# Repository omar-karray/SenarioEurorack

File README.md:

# SenarioEurorack

Senario Looper / MultiFX: a 24HP Eurorack module on a Daisy Seed2 DFM.

| Folder | What |
|---|---|
| [SenarioHW/](SenarioHW/README.md) | the hardware: KiCad project (schematic and primary placement), BOM, design notes |
| [SenarioOS/](SenarioOS/README.md) | the firmware (empty for now; the pin map is in `SenarioOS/docs/pinmap.md`) |
| `KicadLibs/` | git submodule: the shared KiCad libraries (private repository `omar-karray/KicadLibs`) |

## Clone

```bash
git clone --recurse-submodules https://github.com/omar-karray/SenarioEurorack.git
```

The submodule is private: you need access to `omar-karray/KicadLibs`. KiCad 10 resolves the libraries through the project's own tables (`${KIPRJMOD}/../../KicadLibs`), so no global set-up is needed for this project.

Start with [SenarioHW/docs/spec-beta.md](SenarioHW/docs/spec-beta.md) (the version-beta platform spec and how it connects to the Seed2 DFM), then [SenarioHW/docs/design-notes.md](SenarioHW/docs/design-notes.md) (first pass, still valid except where the spec replaces it).

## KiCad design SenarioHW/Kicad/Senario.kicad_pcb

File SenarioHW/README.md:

# SenarioHW

Hardware of the Senario Looper / MultiFX: a 24HP Eurorack module on a Daisy Seed2 DFM.

| Path | What |
|---|---|
| `Kicad/` | the KiCad 10 project `Senario.kicad_pro` (schematic: root + 5 sheets, PCB: primary placement, unrouted) |
| `Kicad/scripts/` | the generators; `design.py` is the design (every part, net and the floorplan) |
| `Kicad/lib/` | project symbols (`Senario.kicad_sym`, generated) |
| `docs/` | `design-notes.md` (read this first), `bom.csv`, `previews/` (schematic PDF, front and back placement, 3D renders), datasheets are in `KicadLibs/datasheets/` |

Libraries come from the `KicadLibs` submodule at the repository root (`${KIPRJMOD}/../../KicadLibs`); stock KiCad libraries for the rest.

## Generated, not drawn

The schematic and the PCB are written by scripts from `Kicad/scripts/design.py`, the same way the Tanghim boards are:

```
cd SenarioHW/Kicad
FORCE=1 scripts/build.sh      # project files, schematic sheets, PCB placement (needs KiCad 10)
scripts/previews.sh           # schematic PDF, front / back PNG, bom.csv
```

`build.sh` refuses to run when `Senario.kicad_pcb` exists, because it **overwrites the schematic and any placement you did by hand**. Use it until you start moving parts in KiCad; from then on edit in KiCad (or export your placement before rebuilding).

Checks that pass on this version: ERC 0 violations; the schematic's netlist and the PCB pad nets are identical (`scripts/check_netlist.py`, 841 pads); DRC shows no placement errors, only the unrouted connections (499) and silkscreen warnings.

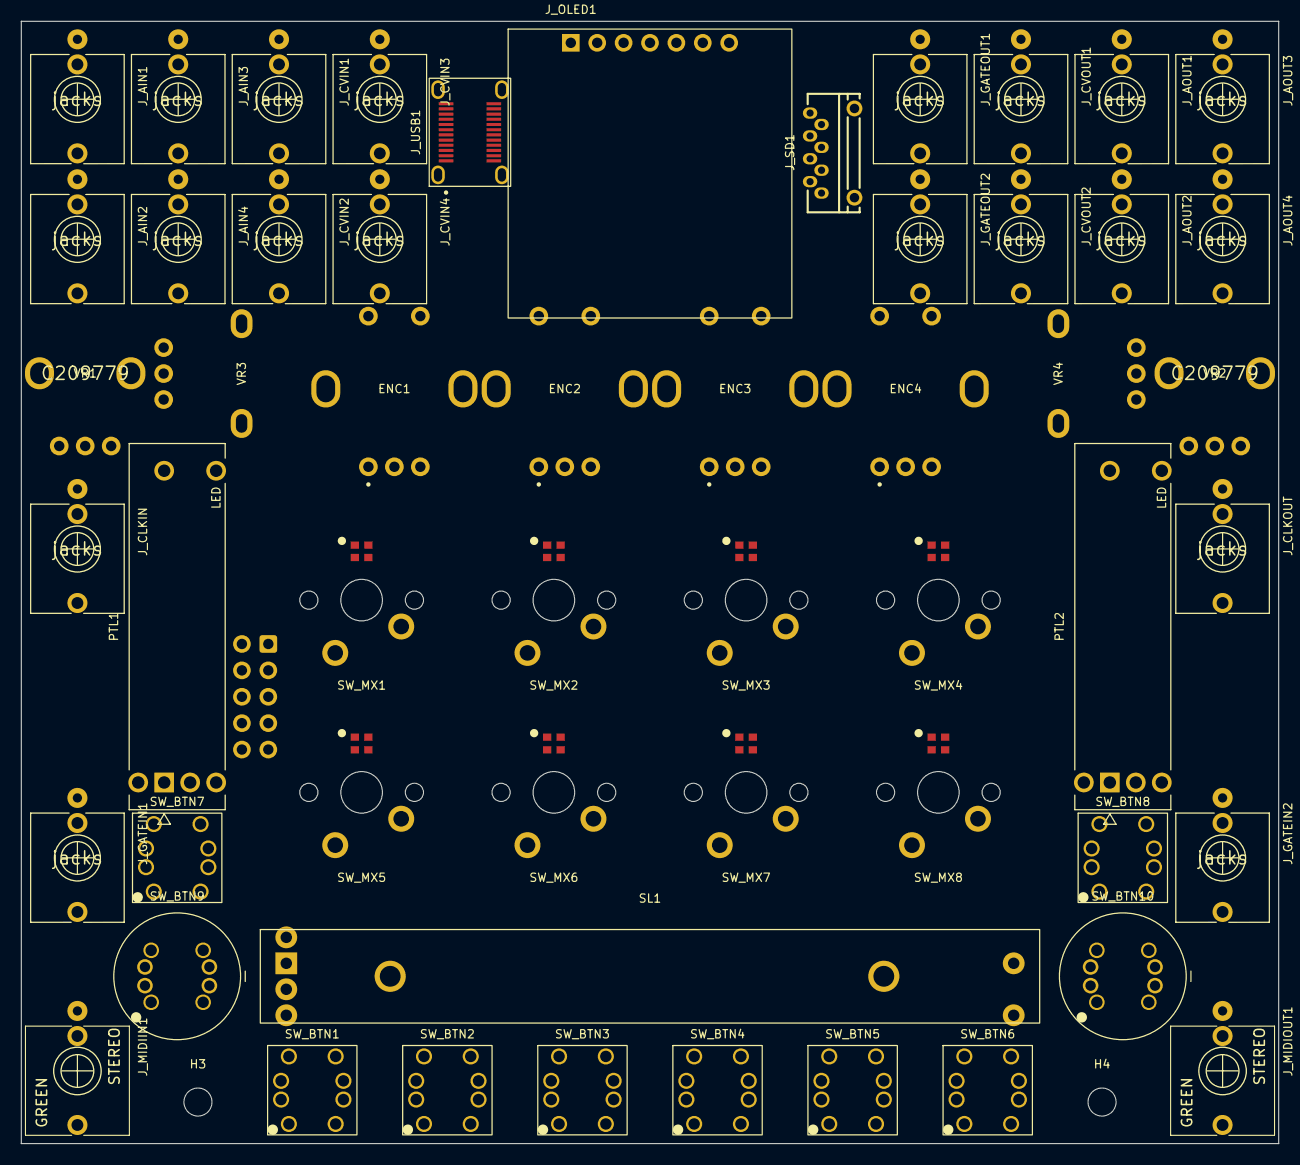
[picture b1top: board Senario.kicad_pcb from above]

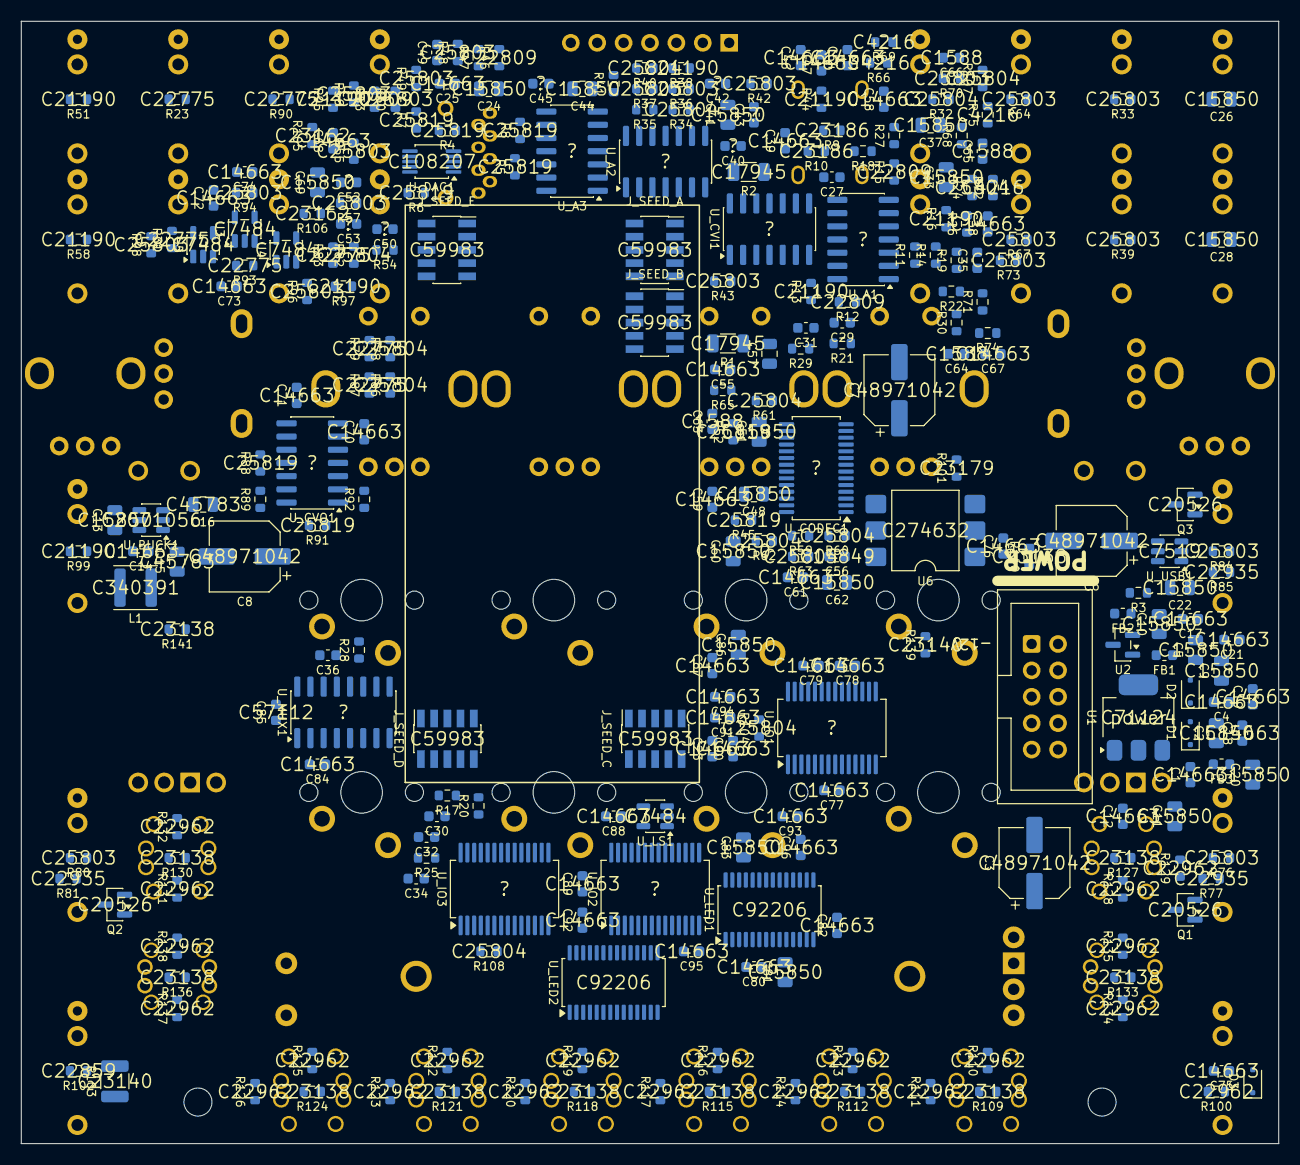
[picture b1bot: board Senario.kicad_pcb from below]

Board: 2 copper layers, 121.0 x 108.0 mm, 337 parts (276 on the bottom side), 274 nets, no tracks yet.

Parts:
C1, C4, C12, C14, C17, C18, C19, C21, C23, C25, C38, C39, C46, C47, C54, C55, C58, C59, C61, C67, C68, C70, C71, C72, C73, C74, C75, C76, C77, C78, C79, C80, C82, C84, C87, C88, C89, C90, C91, C92, C93, C94, C95, C96: 100nF; C_0603_1608Metric
C2, C5, C9, C10, C11, C13, C20, C22, C24, C26, C28, C33, C37, C41, C44, C48, C51, C60, C62, C69, C81, C83, C86: 10uF; C_0805_2012Metric
C3, C6, C7, C8: 100uF; CP_Elec_6.3x7.7
C15, C16: 22uF; C_0805_2012Metric
C27, C29: 220pF; C_0603_1608Metric
C30, C34: 100pF; C_0603_1608Metric
C31, C32, C35, C36: 18pF; C_0603_1608Metric
C40, C42, C43, C45, C49, C50, C52, C53: 47pF; C_0603_1608Metric
C56: 1uF; C_0603_1608Metric
C57: 2.2uF; C_0805_2012Metric
C63, C64, C65, C66: 1nF; C_0603_1608Metric
C85: 10nF; C_0603_1608Metric
D1, D2: NSR1020MW2T3G; D_SOD-323F
D3: 1N5817WS; D_SOD-323F
ENC1, ENC2, ENC3, ENC4: PEC11R-4220K-S0024; Encoder_Bourns_PEC11R-4x20K-S_THT
FACEPLATE1: Faceplate 24HP; Faceplate_24HP
FB1, FB2, FB3: FB 0603; L_0603_1608Metric
H1, H2, H3, H4, H5, H6: M2.5; MountingHole_2.7mm_M2.5
J_AIN1: AIN1; EighthInch_PJ398SM
J_AIN2: AIN2; EighthInch_PJ398SM
J_AIN3: AIN3; EighthInch_PJ398SM
J_AIN4: AIN4; EighthInch_PJ398SM
J_AOUT1: OUT MAIN L; EighthInch_PJ398SM
J_AOUT2: OUT MAIN R; EighthInch_PJ398SM
J_AOUT3: OUT SEND L; EighthInch_PJ398SM
J_AOUT4: OUT SEND R; EighthInch_PJ398SM
J_CLKIN: CLKIN; EighthInch_PJ398SM
J_CLKOUT: CLKOUT; EighthInch_PJ398SM
J_CVIN1: CVIN1; EighthInch_PJ398SM
J_CVIN2: CVIN2; EighthInch_PJ398SM
J_CVIN3: CVIN3; EighthInch_PJ398SM
J_CVIN4: CVIN4; EighthInch_PJ398SM
J_CVOUT1: CVOUT1; EighthInch_PJ398SM
J_CVOUT2: CVOUT2; EighthInch_PJ398SM
J_GATEIN1: GATEIN1; EighthInch_PJ398SM
J_GATEIN2: GATEIN2; EighthInch_PJ398SM
J_GATEOUT1: GATEOUT1; EighthInch_PJ398SM
J_GATEOUT2: GATEOUT2; EighthInch_PJ398SM
J_MIDIIN1: MIDI IN; EighthInch_Stereo_PJ366ST
J_MIDIOUT1: MIDI OUT; EighthInch_Stereo_PJ366ST
J_OLED1: HS96L01W4S03; OLED_0.96in_SPI_Module_HS96L01W4S03
J_PWR1: Eurorack power 10-pin; Pins_2x05_2.54mm_TH_EurorackPower_Shrouded
J_SD1: PJS008U-3000-0 microSD (vertical); CardSlot_MicroSD_YamaichiPJS008U-3000
J_SEED_A: 1.27-2*5PLTM; PinSocket_2x05_P1.27mm_SMD_Boomele_C59983
J_SEED_B: 1.27-2*5PLTM; PinSocket_2x05_P1.27mm_SMD_Boomele_C59983
J_SEED_C: 1.27-2*5PLTM; PinSocket_2x05_P1.27mm_SMD_Boomele_C59983
J_SEED_D: 1.27-2*5PLTM; PinSocket_2x05_P1.27mm_SMD_Boomele_C59983
J_SEED_E: 1.27-2*5PLTM; PinSocket_2x05_P1.27mm_SMD_Boomele_C59983
J_USB1: TYPE-C-31-D-14D; USB_C_Vertical_Hroparts_TYPE-C-31-D-14D_SMD
L1: 4.7uH 2.9A YNR4030-4R7M; L_Changjiang_FNR4030S
PTL1, PTL2: PTL20-15R 10K; Bourns_PTL20_Slide_LED
Q1, Q2, Q3: MMBT3904; SOT-23
R1, R2: 3R3; R_1206_3216Metric
R3: 2K; R_0603_1608Metric
R4, R5, R6, R7, R8, R45, R52, R88, R91: 47K; R_0603_1608Metric
R9, R10: 5K1; R_0603_1608Metric
R11, R14, R18, R21, R26, R29: 66K5; R_0603_1608Metric
R12, R15, R46, R53: 15K; R_0603_1608Metric
R13, R16, R38, R44, R51, R58, R95, R97, R99: 1K; R_0603_1608Metric
R17, R20, R25, R28: 18K; R_0603_1608Metric
R19, R22, R27, R30: 39K; R_0603_1608Metric
R23, R31, R79, R83, R87, R90, R93: 100R; R_0603_1608Metric
R24, R32, R34, R40, R60, R61, R62, R63, R78, R82, R86, R104, R107, R108: 10K; R_0603_1608Metric
R33, R36, R37, R39, R42, R43, R48, R49, R50, R55, R56, R57, R64, R67, R70, R73, R76, R80, R84, R94, R96, R98: 100K; R_0603_1608Metric
R35, R41: 510R; R_0603_1608Metric
R47, R54, R59: 220K; R_0603_1608Metric
R65, R68, R71, R74: 200K; R_0603_1608Metric
R66, R69, R72, R75: 33K; R_0603_1608Metric
R77, R81, R85: 1M; R_0603_1608Metric
R89, R92: 68K; R_0603_1608Metric
R100, R110, R111, R113, R114, R116, R117, R119, R120, R122, R123, R125, R126, R128, R129, R131, R132, R134, R135, R137, R138: 220R; R_0603_1608Metric
R101: 470R; R_0603_1608Metric
R102: 10R; R_0603_1608Metric
R103: 33R; R_1210_3225Metric
R105, R106: 4.7K; R_0603_1608Metric
R109, R112, R115, R118, R121, R124, R127, R130, R133, R136, R140, R141: 330R; R_0603_1608Metric
R139: 33R; R_0603_1608Metric
SL1: Alps RS6011 60mm 10K; ALPS-RS6011_60mm_Panel
SW_BTN1, SW_BTN2, SW_BTN3, SW_BTN4, SW_BTN5, SW_BTN6, SW_BTN7, SW_BTN8: TL1-DNNFN-RCWN RGB; SW_Tact_RGB_Lakeview_TL1-DNNFN-RCWN_THT
SW_BTN9, SW_BTN10: TL16-NND6W-FN RGB; SW_Tact_RGB_Lakeview_TL16-NND6W-FN_THT
SW_MX1, SW_MX2, SW_MX3, SW_MX4, SW_MX5, SW_MX6, SW_MX7, SW_MX8: Cherry MX + SK6812-EC20; SW_Cherry_MX_SK6812-EC20
U1: LD1117S50; SOT-223-3_TabPin2
U2: LM4040DBZ-10; SOT-23
U3, U4, U5: 74AHCT1G125; SOT-23-5
U6: H11L1; SMDIP-6_W9.53mm
U_A1, U_A2, U_A3: TL074; SOIC-14_3.9x8.7mm_P1.27mm
U_BUCK1: AP63205WU-7; SOT-23-6
U_CODEC1: PCM3060PW; TSSOP-28_4.4x9.7mm_P0.65mm
U_CVI1: MCP6004; SOIC-14_3.9x8.7mm_P1.27mm
U_CVO1: TL074; SOIC-14_3.9x8.7mm_P1.27mm
U_DAC1: MCP4728; MSOP-10_3x3mm_P0.5mm
U_IO1, U_IO2, U_IO3: MCP23017; SSOP-28_5.3x10.2mm_P0.65mm
U_LED1, U_LED2: PCA9685PW; TSSOP-28_4.4x9.7mm_P0.65mm
U_LS1: 74AHCT1G125; SOT-23-5
U_MUX1: 74HC4051; SOIC-16_3.9x9.9mm_P1.27mm
U_SEED1: Daisy Seed2 DFM; DAISY_SEED2_DFM_3D
U_USB1: USBLC6-2SC6; SOT-23-6
VR1, VR2: RK09K1130A5R 10K linear (trim, knurled 20 mm); Pot_Rotary_Alps_RK09K-knurl20_THT
VR3, VR4: RD901F-40-15F-B10K-00DL1 (regular); Pot_Rotary_Alpha_RD901F-flat15_THT

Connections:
+3V3: C18.1, C19.1, C20.1, C24.1, C25.1, C59.1, C60.1, C68.1, C69.1, C76.1, C77.1, C78.1, C79.1, C80.1, C81.1, C82.1, C83.1, C86.1, C87.1, J_OLED1.2, J_SD1.4, J_SEED_A.5, J_SEED_A.7, R4.1, R5.1, R6.1, R7.1, R8.1, R59.1, R60.1, R63.1, R78.1, R82.1, R86.1, R101.1, R103.1, R104.1, R105.1, R106.1, R107.1, R108.1, U6.6, U_CODEC1.7, U_DAC1.1, U_IO1.9, U_IO1.18, U_IO2.9, U_IO2.15, U_IO2.18, U_IO3.9, U_IO3.16, U_IO3.18, U_LED1.28, U_LED2.1, U_LED2.28
+3V3A: C21.1, C22.1, C67.1, C84.1, J_SEED_A.9, PTL1.3, PTL2.3, SL1.3, U_CVI1.4, U_MUX1.16, VR1.3, VR2.3, VR3.3, VR4.3
+5V: C11.1, C12.1, C61.1, C62.1, C72.1, C73.1, C74.1, FB3.2, U3.5, U4.5, U5.5, U_CODEC1.24
+5V_LDO: C10.1, FB3.1, U1.2
+5V_LED: C15.1, C16.1, C88.1, C89.1, C90.1, C91.1, C92.1, C93.1, C94.1, C95.1, C96.1, L1.2, R140.1, R141.1, SW_BTN1.8, SW_BTN2.8, SW_BTN3.8, SW_BTN4.8, SW_BTN5.8, SW_BTN6.8, SW_BTN7.8, SW_BTN8.8, SW_BTN9.8, SW_BTN10.8, SW_MX1.5, SW_MX2.5, SW_MX3.5, SW_MX4.5, SW_MX5.5, SW_MX6.5, SW_MX7.5, SW_MX8.5, U_BUCK1.1, U_LS1.5
+5V_USB: J_USB1.A4, J_USB1.A9, J_USB1.B4, J_USB1.B9, U_USB1.5
+12V: C1.1, C2.1, C3.1, C9.1, C13.1, C38.1, C46.1, C54.1, C70.1, D1.1, R1.1, U1.3, U_A1.4, U_A2.4, U_A3.4, U_BUCK1.2, U_BUCK1.3, U_CVO1.4
+12V_FB: D1.2, FB1.2
+12V_IN: FB1.1, J_PWR1.9, J_PWR1.10
-10V_REF: C17.1, R3.2, R65.1, R68.1, R71.1, R74.1, U2.2
-12V: C4.1, C5.1, C6.2, C39.1, C47.1, C55.1, C71.1, D2.2, R3.1, U_A1.11, U_A2.11, U_A3.11, U_CVO1.11
-12V_FB: D2.1, FB2.2
-12V_IN: FB2.1, J_PWR1.1, J_PWR1.2
AIN1_TIP: C26.1, J_AIN1.1
AIN2_TIP: C28.1, J_AIN2.1
AIN3_TIP: J_AIN3.1, R33.1
AIN4_TIP: J_AIN4.1, R39.1
AOUT_ML_TIP: J_AOUT1.1, R23.2
AOUT_MR_TIP: J_AOUT2.1, R31.2
AOUT_SL_TIP: J_AOUT3.1, R51.2
AOUT_SR_TIP: J_AOUT4.1, R58.2
BTN1: SW_BTN1.1, SW_BTN1.3, U_IO1.5
BTN2: SW_BTN2.1, SW_BTN2.3, U_IO1.6
BTN3: SW_BTN3.1, SW_BTN3.3, U_IO1.7
BTN4: SW_BTN4.1, SW_BTN4.3, U_IO1.8
BTN5: SW_BTN5.1, SW_BTN5.3, U_IO2.21
BTN6: SW_BTN6.1, SW_BTN6.3, U_IO2.22
BTN7: SW_BTN7.1, SW_BTN7.3, U_IO2.23
BTN8: SW_BTN8.1, SW_BTN8.3, U_IO2.24
BTN9: SW_BTN9.1, SW_BTN9.2, U_IO2.25
BTN10: SW_BTN10.1, SW_BTN10.2, U_IO2.26
BUCK_BST: C14.1, U_BUCK1.6
BUCK_SW: C14.2, L1.1, U_BUCK1.5
CLKIN_B: Q3.1, R84.2, R85.1
CLKIN_C: Q3.3, R86.2, R87.1
CLKIN_TIP: J_CLKIN.1, R84.1
CLKOUT_BUF: R99.1, U5.4
CLKOUT_TIP: J_CLKOUT.1, R99.2
CLOCK_IN: J_SEED_D.4, R87.2
CLOCK_OUT: J_SEED_C.1, R98.1, U5.2
CVIN1_INV: C63.1, R64.2, R65.2, R66.1, U_CVI1.2
CVIN1_TIP: J_CVIN1.1, R64.1
CVIN2_INV: C64.1, R67.2, R68.2, R69.1, U_CVI1.6
CVIN2_TIP: J_CVIN2.1, R67.1
CVIN3_INV: C65.1, R70.2, R71.2, R72.1, U_CVI1.9
CVIN3_TIP: J_CVIN3.1, R70.1
CVIN4_INV: C66.1, R73.2, R74.2, R75.1, U_CVI1.13
CVIN4_TIP: J_CVIN4.1, R73.1
CVO1_INV: R88.1, R89.1, U_CVO1.2
CVO1_OUT: R89.2, R90.1, U_CVO1.1
CVO2_INV: R91.1, R92.1, U_CVO1.6
CVO2_OUT: R92.2, R93.1, U_CVO1.7
CVOUT1_TIP: J_CVOUT1.1, R90.2
CVOUT2_TIP: J_CVOUT2.1, R93.2
CV_IN_1_ADC: C63.2, J_SEED_C.9, R66.2, U_CVI1.1
CV_IN_2_ADC: C64.2, J_SEED_C.7, R69.2, U_CVI1.7
CV_IN_3_ADC: C65.2, J_SEED_C.10, R72.2, U_CVI1.8
CV_IN_4_ADC: C66.2, J_SEED_C.2, R75.2, U_CVI1.14
CV_OUT_1_DAC: U_CVO1.3, U_DAC1.6
CV_OUT_2_DAC: U_CVO1.5, U_DAC1.7
DSY_VIN: C8.1, J_SEED_A.1, J_SEED_A.3, R2.2
DSY_VIN_A: C7.1, R1.2, R2.1
E0_AC: C41.2, R36.1
E0_INV1: C40.1, R33.2, R34.1, U_A2.2
E0_INV2: C42.1, R36.2, R37.1, U_A2.13
E0_MID1: R34.2, R35.1
E0_OUT1: C40.2, C41.1, R35.2, U_A2.1
E0_OUT2: C42.2, R37.2, R38.1, U_A2.14
E1_AC: C44.2, R42.1
E1_INV1: C43.1, R39.2, R40.1, U_A2.6
E1_INV2: C45.1, R42.2, R43.1, U_A2.9
E1_MID1: R40.2, R41.1
E1_OUT1: C43.2, C44.1, R41.2, U_A2.7
E1_OUT2: C45.2, R43.2, R44.1, U_A2.8
ENC1_A: ENC1.A, U_IO1.21
ENC1_B: ENC1.B, U_IO1.22
ENC1_SW: ENC1.S1, U_IO1.23
ENC2_A: ENC2.A, U_IO1.24
ENC2_B: ENC2.B, U_IO1.25
ENC2_SW: ENC2.S1, U_IO1.26
ENC3_A: ENC3.A, U_IO1.27
ENC3_B: ENC3.B, U_IO1.28
ENC3_SW: ENC3.S1, U_IO1.1
ENC4_A: ENC4.A, U_IO1.2
ENC4_B: ENC4.B, U_IO1.3
ENC4_SW: ENC4.S1, U_IO1.4
EXT_IN_L: R38.2, U_CODEC1.25
EXT_IN_R: R44.2, U_CODEC1.26
EXT_OUT_L: C48.1, U_CODEC1.20
EXT_OUT_R: C51.1, U_CODEC1.18
GATEIN1_B: Q1.1, R76.2, R77.1
GATEIN1_C: Q1.3, R78.2, R79.1
GATEIN1_TIP: J_GATEIN1.1, R76.1
GATEIN2_B: Q2.1, R80.2, R81.1
GATEIN2_C: Q2.3, R82.2, R83.1
GATEIN2_TIP: J_GATEIN2.1, R80.1
GATEOUT1_BUF: R95.1, U3.4
GATEOUT1_TIP: J_GATEOUT1.1, R95.2
GATEOUT2_BUF: R97.1, U4.4
GATEOUT2_TIP: J_GATEOUT2.1, R97.2
GATE_IN_1: J_SEED_C.3, R79.2
GATE_IN_2: J_SEED_D.6, R83.2
GATE_OUT_1: J_SEED_C.5, R94.1, U3.2
GATE_OUT_2: J_SEED_C.4, R96.1, U4.2
GND: C1.2, C2.2, C3.2, C4.2, C5.2, C6.1, C7.2, C8.2, C9.2, C10.2, C11.2, C12.2, C13.2, C15.2, C16.2, C17.2, C18.2, C19.2, C20.2, C21.2, C22.2, C23.2, C24.2, C25.2, C30.2, C32.2, C34.2, C36.2, C38.2, C39.2, C46.2, C47.2, C54.2, C55.2, C56.2, C57.2, C58.2, C59.2, C60.2, C61.2, C62.2, C67.2, C68.2, C69.2, C70.2, C71.2, C72.2, C73.2, C74.2, C75.2, C76.2, C77.2, C78.2, C79.2, C80.2, C81.2, C82.2, C83.2, C84.2, C85.2, C86.2, C87.2, C88.2, C89.2, C90.2, C91.2, C92.2, C93.2, C94.2, C95.2, C96.2, ENC1.C, ENC1.S2, ENC2.C, ENC2.S2, ENC3.C, ENC3.S2, ENC4.C, ENC4.S2, J_AIN1.2, J_AIN1.3, J_AIN2.2, J_AIN2.3, J_AIN3.2, J_AIN3.3, J_AIN4.2, J_AIN4.3, J_AOUT1.2, J_AOUT2.2, J_AOUT3.2, J_AOUT4.2, J_CLKIN.2, J_CLKIN.3, J_CLKOUT.2, J_CVIN1.2, J_CVIN1.3, J_CVIN2.2, J_CVIN2.3, J_CVIN3.2, J_CVIN3.3, J_CVIN4.2, J_CVIN4.3, J_CVOUT1.2, J_CVOUT2.2, J_GATEIN1.2, J_GATEIN1.3, J_GATEIN2.2, J_GATEIN2.3, J_GATEOUT1.2, J_GATEOUT2.2, J_MIDIOUT1.2, J_OLED1.1, J_OLED1.7, J_PWR1.3, J_PWR1.4, J_PWR1.5, J_PWR1.6, J_PWR1.7, J_PWR1.8, J_SD1.6, J_SD1.9, J_SD1.10, J_SEED_A.2, J_SEED_A.4, J_SEED_A.6, J_SEED_A.8, J_SEED_A.10, J_USB1.A1, J_USB1.A12, J_USB1.B1, J_USB1.B12, J_USB1.SH, PTL1.1, PTL2.1, Q1.2, Q2.2, Q3.2, R9.2, R10.2, R24.2, R32.2, R45.2, R52.2, R61.2, R62.2, R77.2, R81.2, R85.2, R88.2, R91.2, R94.2, R96.2, R98.2, SL1.1, SW_BTN1.2, SW_BTN1.4, SW_BTN2.2, SW_BTN2.4, SW_BTN3.2, SW_BTN3.4, SW_BTN4.2, SW_BTN4.4, SW_BTN5.2, SW_BTN5.4, SW_BTN6.2, SW_BTN6.4, SW_BTN7.2, SW_BTN7.4, SW_BTN8.2, SW_BTN8.4, SW_BTN9.3, SW_BTN9.4, SW_BTN10.3, SW_BTN10.4, SW_MX1.2, SW_MX1.3, SW_MX2.2, SW_MX2.3, SW_MX3.2, SW_MX3.3, SW_MX4.2, SW_MX4.3, SW_MX5.2, SW_MX5.3, SW_MX6.2, SW_MX6.3, SW_MX7.2, SW_MX7.3, SW_MX8.2, SW_MX8.3, U1.1, U2.1, U3.1, U3.3, U4.1, U4.3, U5.1, U5.3, U6.5, U_A2.3, U_A2.5, U_A3.3, U_A3.5, U_A3.10, U_A3.12, U_BUCK1.4, U_CODEC1.8, U_CODEC1.16, U_CODEC1.22, U_CODEC1.23, U_CVI1.3, U_CVI1.5, U_CVI1.10, U_CVI1.11, U_CVI1.12, U_CVO1.10, U_CVO1.12, U_DAC1.4, U_DAC1.10, U_IO1.10, U_IO1.15, U_IO1.16, U_IO1.17, U_IO2.10, U_IO2.16, U_IO2.17, U_IO3.10, U_IO3.15, U_IO3.17, U_LED1.1, U_LED1.2, U_LED1.3, U_LED1.4, U_LED1.5, U_LED1.14, U_LED1.24, U_LED1.25, U_LED2.2, U_LED2.3, U_LED2.4, U_LED2.5, U_LED2.14, U_LED2.24, U_LED2.25, U_LS1.1, U_LS1.3, U_MUX1.6, U_MUX1.7, U_MUX1.8, U_USB1.2, VR1.1, VR2.1, VR3.1, VR4.1
I2C_INT: J_SEED_C.6, R104.2, U_IO1.19, U_IO1.20, U_IO2.19, U_IO2.20, U_IO3.19, U_IO3.20
I2C_SCL: J_SEED_B.8, R105.2, U_DAC1.2, U_IO1.12, U_IO2.12, U_IO3.12, U_LED1.26, U_LED2.26
I2C_SDA: J_SEED_B.6, R106.2, U_DAC1.3, U_IO1.13, U_IO2.13, U_IO3.13, U_LED1.27, U_LED2.27
LED_BTN1_B_K: R111.1, U_LED1.8
LED_BTN1_B_LK: R111.2, SW_BTN1.7
LED_BTN1_G_K: R110.1, U_LED1.7
LED_BTN1_G_LK: R110.2, SW_BTN1.6
LED_BTN1_R_K: R109.1, U_LED1.6
LED_BTN1_R_LK: R109.2, SW_BTN1.5
LED_BTN2_B_K: R114.1, U_LED1.11
LED_BTN2_B_LK: R114.2, SW_BTN2.7
LED_BTN2_G_K: R113.1, U_LED1.10
LED_BTN2_G_LK: R113.2, SW_BTN2.6
LED_BTN2_R_K: R112.1, U_LED1.9
LED_BTN2_R_LK: R112.2, SW_BTN2.5
LED_BTN3_B_K: R117.1, U_LED1.15
LED_BTN3_B_LK: R117.2, SW_BTN3.7
LED_BTN3_G_K: R116.1, U_LED1.13
LED_BTN3_G_LK: R116.2, SW_BTN3.6
LED_BTN3_R_K: R115.1, U_LED1.12
LED_BTN3_R_LK: R115.2, SW_BTN3.5
LED_BTN4_B_K: R120.1, U_LED1.18
LED_BTN4_B_LK: R120.2, SW_BTN4.7
LED_BTN4_G_K: R119.1, U_LED1.17
LED_BTN4_G_LK: R119.2, SW_BTN4.6
LED_BTN4_R_K: R118.1, U_LED1.16
LED_BTN4_R_LK: R118.2, SW_BTN4.5
LED_BTN5_B_K: R123.1, U_LED1.21
LED_BTN5_B_LK: R123.2, SW_BTN5.7
LED_BTN5_G_K: R122.1, U_LED1.20
LED_BTN5_G_LK: R122.2, SW_BTN5.6
LED_BTN5_R_K: R121.1, U_LED1.19
LED_BTN5_R_LK: R121.2, SW_BTN5.5
LED_BTN6_B_K: R126.1, U_LED2.8
LED_BTN6_B_LK: R126.2, SW_BTN6.7
LED_BTN6_G_K: R125.1, U_LED2.7
LED_BTN6_G_LK: R125.2, SW_BTN6.6
LED_BTN6_R_K: R124.1, U_LED2.6
LED_BTN6_R_LK: R124.2, SW_BTN6.5
LED_BTN7_B_K: R129.1, U_LED2.11
LED_BTN7_B_LK: R129.2, SW_BTN7.7
LED_BTN7_G_K: R128.1, U_LED2.10
LED_BTN7_G_LK: R128.2, SW_BTN7.6
LED_BTN7_R_K: R127.1, U_LED2.9
LED_BTN7_R_LK: R127.2, SW_BTN7.5
LED_BTN8_B_K: R132.1, U_LED2.15
LED_BTN8_B_LK: R132.2, SW_BTN8.7
LED_BTN8_G_K: R131.1, U_LED2.13
LED_BTN8_G_LK: R131.2, SW_BTN8.6
LED_BTN8_R_K: R130.1, U_LED2.12
LED_BTN8_R_LK: R130.2, SW_BTN8.5
LED_BTN9_B_K: R135.1, U_LED2.18
LED_BTN9_B_LK: R135.2, SW_BTN9.7
LED_BTN9_G_K: R134.1, U_LED2.17
LED_BTN9_G_LK: R134.2, SW_BTN9.6
LED_BTN9_R_K: R133.1, U_LED2.16
LED_BTN9_R_LK: R133.2, SW_BTN9.5
LED_BTN10_B_K: R138.1, U_LED2.21
LED_BTN10_B_LK: R138.2, SW_BTN10.7
LED_BTN10_G_K: R137.1, U_LED2.20
LED_BTN10_G_LK: R137.2, SW_BTN10.6
LED_BTN10_R_K: R136.1, U_LED2.19
LED_BTN10_R_LK: R136.2, SW_BTN10.5
LED_DATA: J_SEED_B.1, U_LS1.2
LED_DATA_5V: R139.1, U_LS1.4
LED_OE: R108.2, U_IO3.24, U_LED1.23, U_LED2.23
LED_PTL1_A: PTL1.B, R140.2
LED_PTL1_K: PTL1.E, U_LED1.22
LED_PTL2_A: PTL2.B, R141.2
LED_PTL2_K: PTL2.E, U_LED2.22
MIDI_IN_RING: J_MIDIIN1.3, R100.1
MIDI_IN_SH: C75.1, J_MIDIIN1.2
MIDI_IN_TIP: D3.2, J_MIDIIN1.1, U6.2
MIDI_OPTO_A: D3.1, R100.2, U6.1
MIDI_OUT_RING: J_MIDIOUT1.3, R103.2
MIDI_OUT_TIP: J_MIDIOUT1.1, R102.2
MIDI_RX: J_SEED_B.9, R101.2, U6.4
MIDI_TX: J_SEED_B.5, R102.1
MUX_A: U_IO3.21, U_MUX1.11
MUX_B: U_IO3.22, U_MUX1.10
MUX_C: U_IO3.23, U_MUX1.9
MX1: SW_MX1.1, U_IO2.27
MX2: SW_MX2.1, U_IO2.28
MX3: SW_MX3.1, U_IO2.1
MX4: SW_MX4.1, U_IO2.2
MX5: SW_MX5.1, U_IO2.3
MX6: SW_MX6.1, U_IO2.4
MX7: SW_MX7.1, U_IO2.5
MX8: SW_MX8.1, U_IO2.6
MXL_DIN1: R139.2, SW_MX1.4
MXL_DOUT1: SW_MX1.6, SW_MX2.4
MXL_DOUT2: SW_MX2.6, SW_MX3.4
MXL_DOUT3: SW_MX3.6, SW_MX4.4
MXL_DOUT4: SW_MX4.6, SW_MX5.4
MXL_DOUT5: SW_MX5.6, SW_MX6.4
MXL_DOUT6: SW_MX6.6, SW_MX7.4
MXL_DOUT7: SW_MX7.6, SW_MX8.4
OLED_DC: J_OLED1.6, J_SEED_B.10
OLED_MOSI: J_OLED1.4, J_SEED_B.7
OLED_RES: J_OLED1.5, R107.2, U_IO3.25
OLED_SCK: J_OLED1.3, J_SEED_B.3
PCM_DEMP: R61.1, U_CODEC1.2
PCM_FMT: R60.2, U_CODEC1.1
PCM_IFMD: R62.1, U_CODEC1.27
PCM_MODE: R59.2, U_CODEC1.28
PCM_RST: C56.1, R63.2, U_CODEC1.15
POT_MUX: C85.1, J_SEED_C.8, U_MUX1.3
SAI2_FS: J_SEED_D.2, U_CODEC1.4, U_CODEC1.11
SAI2_MCLK: J_SEED_E.1, U_CODEC1.6, U_CODEC1.9
SAI2_SCK: J_SEED_E.7, U_CODEC1.5, U_CODEC1.10
SAI2_SD_A: J_SEED_E.5, U_CODEC1.12
SAI2_SD_B: J_SEED_E.3, U_CODEC1.3
SDMMC_CK: J_SD1.5, J_SEED_E.9
SDMMC_CMD: J_SD1.3, J_SEED_E.10, R4.2
SDMMC_D0: J_SD1.7, J_SEED_E.8, R5.2
SDMMC_D1: J_SD1.8, J_SEED_E.6, R6.2
SDMMC_D2: J_SD1.1, J_SEED_E.4, R7.2
SDMMC_D3: J_SD1.2, J_SEED_E.2, R8.2
SEED_IN_L: J_SEED_D.1, R13.2
SEED_IN_R: J_SEED_D.3, R16.2
SEED_OUT_L+: J_SEED_D.9, R17.1
SEED_OUT_L-: J_SEED_D.7, R20.1
SEED_OUT_R+: J_SEED_D.10, R25.1
SEED_OUT_R-: J_SEED_D.8, R28.1
SIN_L_C: C26.2, R11.1
SIN_L_INV: C27.1, R11.2, R12.1, U_A1.2
SIN_L_OUT: C27.2, R12.2, R13.1, U_A1.1
SIN_R_C: C28.2, R14.1
SIN_R_INV: C29.1, R14.2, R15.1, U_A1.6
SIN_R_OUT: C29.2, R15.2, R16.1, U_A1.7
SOL_A: C30.1, R17.2, R18.1
SOL_AC: C33.2, R23.1, R24.1
SOL_B: C32.1, R20.2, R21.1
SOL_INV: C31.1, R18.2, R19.1, U_A1.9
SOL_NI: R21.2, R22.1, U_A1.10
SOL_OUT: C31.2, C33.1, R19.2, U_A1.8
SOR_A: C34.1, R25.2, R26.1
SOR_AC: C37.2, R31.1, R32.1
SOR_B: C36.1, R28.2, R29.1
SOR_INV: C35.1, R26.2, R27.1, U_A1.13
SOR_NI: R29.2, R30.1, U_A1.12
SOR_OUT: C35.2, C37.1, R27.2, U_A1.14
UNUSED_U_CVO1_3: U_CVO1.8, U_CVO1.9
UNUSED_U_CVO1_4: U_CVO1.13, U_CVO1.14
USB_CC1: J_USB1.A5, R9.1
USB_CC2: J_USB1.B5, R10.1
USB_IN_N: J_USB1.A7, J_USB1.B7, U_USB1.3
USB_IN_P: J_USB1.A6, J_USB1.B6, U_USB1.1
USB_OTG_HS_N: J_SEED_B.2, U_USB1.4
USB_OTG_HS_P: J_SEED_B.4, U_USB1.6
VCOM_EXT: C57.1, C58.1, U_A2.10, U_A2.12, U_CODEC1.21
VCOM_SEED: C23.1, J_SEED_D.5, R22.2, R30.2, U_A1.3, U_A1.5
WIP_POT1: U_MUX1.12, VR1.2
WIP_POT2: U_MUX1.1, VR2.2
WIP_POT3: U_MUX1.5, VR3.2
WIP_POT4: U_MUX1.2, VR4.2
WIP_PTL1: PTL1.2, U_MUX1.13
WIP_PTL2: PTL2.2, U_MUX1.14
WIP_SL: SL1.2, U_MUX1.15
X0_AC: C48.2, R45.1, R46.1, R47.1
X0_INV1: C49.1, R46.2, R47.2, R48.1, U_A3.2
X0_INV2: C50.1, R49.2, R50.1, U_A3.13
X0_OUT1: C49.2, R48.2, R49.1, U_A3.1
X0_OUT2: C50.2, R50.2, R51.1, U_A3.14
X1_AC: C51.2, R52.1, R53.1, R54.1
X1_INV1: C52.1, R53.2, R54.2, R55.1, U_A3.6
X1_INV2: C53.1, R56.2, R57.1, U_A3.9
X1_OUT1: C52.2, R55.2, R56.1, U_A3.7
X1_OUT2: C53.2, R57.2, R58.1, U_A3.8

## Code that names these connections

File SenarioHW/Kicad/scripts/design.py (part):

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N_CVIN = 4                                                                                  # CV in 1-4 (Dev Kit stage, MCP6004 quad)
GATES_IN = [("GATEIN1", "GATE_IN_1"), ("GATEIN2", "GATE_IN_2"), ("CLKIN", "CLOCK_IN")]      # (jack name, net)
GATES_OUT = [("GATEOUT1", "GATE_OUT_1"), ("GATEOUT2", "GATE_OUT_2"), ("CLKOUT", "CLOCK_OUT")]
N_BTN = 10                                                                                  # BTN1-6 control row, BTN7 / BTN8 beside the sliders (TL1), BTN9 / BTN10 at the Alps slider (TL16)
OLED_MODEL = "0.96"                                                                         # "0.96" (HS96L01W4S03, in use) or "1.3" (HS13L01W4S01): the schematic, footprint and faceplate window follow
# CV out stage (Dev Kit: DAC -> TL074 non-inverting, 0 .. 5 V). The MCP4728 runs from 3V3 with its internal 2.048 V reference at gain 1 (its I2C inputs need VIH = 0.7 x VDD, which 3.3 V
# does not meet at VDD = 5 V), so the stage needs a gain of 5 / 2.048 = 2.44: 1 + Rf / Rg = 1 + 68K / 47K = 2.447 -> 5.01 V. CHANGE THESE TWO when the stage is redefined (full +-10 V Eurorack).
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        CP("100uF", rail if rail == "+12V" else "GND", "GND" if rail == "+12V" else rail)

with blk("Power", "seedpwr"):
    # Seed supply: 2 x 3R3 + 2 x 100 uF (Dev Kit); placed next to the Seed's socket A (the DSY_VIN pins), in the free space of the right column
    R("3R3", "+12V", "DSY_VIN_A", fp=FP_R1206)
    R("3R3", "DSY_VIN_A", "DSY_VIN", fp=FP_R1206)
    CP("100uF", "DSY_VIN_A", "GND")
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
# ================================================================== DAISY SEED2 DFM
SEED_PINS = {
    "D0": "CLOCK_IN", "D1": "SDMMC_D3", "D2": "SDMMC_D2", "D3": "SDMMC_D1", "D4": "SDMMC_D0",       # D1-D6 are the SDMMC1 pins (4-bit, as the Dev Kit microSD slot)
    "D5": "SDMMC_CMD", "D6": "SDMMC_CK", "D7": "OLED_DC", "D8": "OLED_SCK", "D9": "LED_DATA", "D10": "OLED_MOSI",
    "D11": "I2C_SCL", "D12": "I2C_SDA", "D13": "MIDI_TX", "D14": "MIDI_RX",
    "D15": "POT_MUX", "D16": "CLOCK_OUT", "D17": "CV_IN_1_ADC", "D18": "CV_IN_2_ADC", "D19": "GATE_IN_1",
    "D20": "GATE_OUT_1", "D21": "CV_IN_3_ADC", "D22": "GATE_OUT_2", "D23": "I2C_INT",                 # D22 / D23 (the Seed DACs) are plain GPIO now: the CV outs are on the MCP4728
    "D24": "SAI2_MCLK", "D25": "SAI2_SD_B", "D26": "SAI2_SD_A", "D27": "SAI2_FS", "D28": "SAI2_SCK",
    "D29": "USB_OTG_HS_N", "D30": "USB_OTG_HS_P", "D31": "CV_IN_4_ADC", "D32": "GATE_IN_2",
    "VIN": "DSY_VIN", "3V3_D": "+3V3", "3V3_A": "+3V3A", "GND": "GND",
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    # inputs: 10u coupling, 66K5, TL074 inverting, 15K || 220p, VCOM reference
    jack("AIN1", "AIN1_TIP")
    jack("AIN2", "AIN2_TIP")
    jack("AOUT1", "AOUT_ML_TIP", sw=None, label="OUT MAIN L")
    jack("AOUT2", "AOUT_MR_TIP", sw=None, label="OUT MAIN R")
    for ch, (tip, inn, outn) in {"L": ("AIN1_TIP", "SEED_IN_L", "SEED_AIN_L_NODE"),
                                  "R": ("AIN2_TIP", "SEED_IN_R", "SEED_AIN_R_NODE")}.items():
        pass
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with blk("Audio_Ext", "audio_ext"):
    jack("AIN3", "AIN3_TIP")
    jack("AIN4", "AIN4_TIP")
    jack("AOUT3", "AOUT_SL_TIP", sw=None, label="OUT SEND L")
    jack("AOUT4", "AOUT_SR_TIP", sw=None, label="OUT SEND R")
    # inputs: 100K -> TL074 inverting (10K + 510R || 47p) -> 10u -> 100K -> TL074 inverting (100K || 47p) referenced to VCOM -> 1K
    for k, (tip, final) in enumerate((("AIN3_TIP", "EXT_IN_L"), ("AIN4_TIP", "EXT_IN_R"))):
        n = f"E{k}"
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    MX = [f"MX{i}" for i in range(1, 9)]
    io1 = [s for e in ENC for s in e] + BTN[:4]               # 12 + 4 = 16
    io2 = BTN[4:] + MX                                          # 6 + 8 = 14 (2 spare)
    io3 = ["MUX_A", "MUX_B", "MUX_C", "LED_OE", "OLED_RES"]    # outputs (firmware sets them); 11 spare. They left the Seed to free its pins.
    for ref_, a, sigs in (("U_IO1", (0, 0, 0), io1), ("U_IO2", (1, 0, 0), io2), ("U_IO3", (0, 1, 0), io3)):      # 0x20, 0x21, 0x22
        pins = {"V_{DD}": "+3V3", "V_{SS}": "GND", "SCK": "I2C_SCL", "SDA": "I2C_SDA",
                "A0": "+3V3" if a[0] else "GND", "A1": "+3V3" if a[1] else "GND", "A2": "+3V3" if a[2] else "GND", "~{RESET}": "+3V3",
                "INTA": "I2C_INT", "INTB": "I2C_INT"}
        gpio = [f"GPA{i}" for i in range(8)] + [f"GPB{i}" for i in range(8)]
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    R("4.7K", "+3V3", "I2C_SCL")
    R("4.7K", "+3V3", "I2C_SDA")
    if OLED_MODEL == "0.96":
        R("10K", "+3V3", "OLED_RES")                   # the 0.96 in module has a RES pin: not held in reset until the firmware drives it

with blk("Digital_IO", "leddrv"):
    # LED drivers: PCA9685 open drain, LED anodes on +5V_LED, resistors in series with the cathodes (on the panel sheet). 0x40: BTN1-5 RGB (15) + PTL1. 0x41: BTN6-10 RGB (15) + PTL2.
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
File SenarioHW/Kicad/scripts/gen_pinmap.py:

#!/usr/bin/env python3
"""Write SenarioOS/docs/pinmap.md from design.py (the firmware's view of the hardware): Seed pins, I2C devices (from the part list), mux channels, notes."""
import re, sys
from pathlib import Path
sys.path.insert(0, str(Path(__file__).parent))
import design as D

names = {"D0": "PB12", "D1": "PC11", "D2": "PC10", "D3": "PC9", "D4": "PC8", "D5": "PD2", "D6": "PC12", "D7": "PG10", "D8": "PG11",
         "D9": "PB4", "D10": "PB5", "D11": "PB8", "D12": "PB9", "D13": "PB6", "D14": "PB7", "D15": "PC0", "D16": "PA3", "D17": "PB1",
         "D18": "PA7", "D19": "PA6", "D20": "PC1", "D21": "PC4", "D22": "PA5", "D23": "PA4", "D24": "PA1", "D25": "PA0", "D26": "PD11",
         "D27": "PG9", "D28": "PA2", "D29": "PB14", "D30": "PB15", "D31": "PC2", "D32": "PC3"}
fn = {"D1": "SDMMC1_D3", "D2": "SDMMC1_D2", "D3": "SDMMC1_D1", "D4": "SDMMC1_D0", "D5": "SDMMC1_CMD", "D6": "SDMMC1_CK",
      "D7": "GPIO (OLED D/C)", "D8": "SPI1_SCK", "D9": "GPIO (SK6812 data: TIM3_CH1 on PB4, CHECK the alternate function)", "D10": "SPI1_MOSI",
      "D11": "I2C1_SCL", "D12": "I2C1_SDA", "D13": "USART1_TX", "D14": "USART1_RX", "D15": "ADC (A0)", "D16": "GPIO (output only on the Seed2: clock out)",
      "D17": "ADC (A2)", "D18": "ADC (A3)", "D19": "GPIO (ADC-capable)", "D20": "GPIO (ADC-capable)", "D21": "ADC (A6)", "D22": "GPIO (a DAC pin, unused as DAC)",
      "D23": "GPIO (a DAC pin, unused as DAC)", "D24": "SAI2_MCLK_B", "D25": "SAI2_SD_B", "D26": "SAI2_SD_A", "D27": "SAI2_FS_B", "D28": "SAI2_SCK_B",
      "D29": "USB_OTG_HS", "D30": "USB_OTG_HS", "D31": "ADC (PC2)", "D32": "GPIO (ADC-capable)"}
rows = ["# Seed2 DFM pin map (generated by SenarioHW/Kicad/scripts/gen_pinmap.py from design.py; version-beta, docs/spec-beta.md section 2.2)\n",
        "Daisy pin | STM32 | Function | Net\n--- | --- | --- | ---"]
for k in [f"D{i}" for i in range(33)]:
    rows.append(f"{k} | {names[k]} | {fn.get(k, 'GPIO')} | {D.SEED_PINS.get(k) or '(free)'}")
rows.append("\nAudio pads: AUDIO_IN_1/2 = `SEED_IN_L/R`, OUT 1 = left (+/-), OUT 2 = right (+/-), VCOM = `VCOM_SEED`.")
rows.append("\nAll 33 pins are used. D1-D6 = SDMMC1 (4-bit microSD, as the Seed3 Eurorack Dev Kit), D29 / D30 = USB HS (the panel USB-C: USB MIDI; **firmware update over it is NOT settled**: the STM32 ROM DFU listens on the "
            "Seed's own micro-USB), D22 / D23 (the Seed's DACs) are GPIO because the CV outs are on an MCP4728. D16 is output only (clock out). The OLED's CS is tied low in hardware; its RES is on `U_IO3`.")


def devs(prefix):
    return [p for p in D.PARTS if p["ref"].startswith(prefix)]


def pin_list(p):
    return ", ".join(f"{k}={v}" for k, v in p["pins"].items() if re.match(r"GP[AB]\d|LED\d+$", k) and v)


rows.append("""
## I2C devices (I2C1, 4.7K pull-ups, 400 kHz to 1 MHz)

Address | Device | Job
--- | --- | ---""")
for ref, addr in (("U_IO1", "0x20"), ("U_IO2", "0x21"), ("U_IO3", "0x22")):
    p = next(q for q in D.PARTS if q["ref"] == ref)
    rows.append(f"{addr} | MCP23017 `{ref}` | {pin_list(p)}. INTA / INTB are open drain, wired together to `I2C_INT` (D23). Inputs: enable the internal pull-ups (GPPU); all switches are plain switches to GND (the standard Bourns encoders have no LED).")
rows.append("0x60 | MCP4728 `U_DAC1` | 4-channel 12-bit DAC: **A = CV out 1, B = CV out 2** (C, D spare), VDD 3V3, internal 2.048 V reference, gain 1; the op-amp stage scales to 0 .. 5 V (`CVO_RF` / `CVO_RG` in design.py). Control rate (about 1 kHz). LDAC tied low. Write the CV first and raise a gate 1 to 2 ms later.")
for ref, addr in (("U_LED1", "0x40"), ("U_LED2", "0x41")):
    p = next(q for q in D.PARTS if q["ref"] == ref)
    rows.append(f"{addr} | PCA9685 `{ref}` | {pin_list(p)} (open drain, common-anode LEDs on +5V_LED, `LED_OE` high = off)")
rows.append("""
PCA9685: set OUTDRV = 0 (open drain), clear ALLCALL; the MCP4728 and the PCA9685 both answer the I2C general call: check the datasheets before sending a general-call reset.

## SK6812 chain (8 x SK6812-EC20 under the MX keys)

`LED_DATA` (D9) -> 74AHCT1G125 on +5V_LED (`U_LS1`) -> 33R -> key 1 DIN ... key 8 DIN. Drive it from a timer + DMA (or SPI), 800 kHz; keep the brightness low (the 5 V budget).

## Panel analog (74HC4051 `U_MUX1`, ADC on D15, select lines `MUX_A/B/C` from `U_IO3`)

Channel | Control
--- | ---
0 | PTL1 wiper (Bourns PTL20, left)
1 | PTL2 wiper (Bourns PTL20, right)
2 | Alps RS6011 slider (60 mm)
3 | VR1 (trim, left)
4 | VR2 (trim, right)
5 | VR3 (regular pot, left)
6 | VR4 (regular pot, right)
7 | free

## Notes for the firmware

- External codec PCM3060 on SAI2 in H/W mode: slave, 24-bit left-justified, single-ended, de-emphasis off. The Seed drives MCLK/SCK/FS (SAI2 block B master), SD_A = DAC data to the codec, SD_B = ADC data from it. Check against libDaisy's Daisy Patch SAI2 set-up.
- CV in (4): inverting stage, +-5 V maps to 3.3 .. 0 V (invert in firmware). Gate in (2) and clock in (1): inverting transistor stage (a high gate reads 0). Clock in is on D0 (EXTI12), gate in 1 / 2 on D19 / D32.
- CV out (2): MCP4728, 0 .. 5 V, control rate. Gate out (2) and clock out (1): 0 / 5 V buffers on D20 / D22 / D16, set from the audio callback (a small block size keeps the jitter low) or a timer.
- MIDI TX should be open drain if the HAL allows it (a mono TS cable in the TRS jack shorts the ring to the sleeve).
- OLED: SPI1 write-only, 4-wire (SCK D8, MOSI D10, D/C D7), CS tied low, RES from `U_IO3` GPB. The 0.96 in module is an SSD1315; the 1.3 in (alternative in KicadLibs) is an SH1106 (libDaisy has `oled_sh1106.h`).
""")
out = Path(sys.argv[1]) if len(sys.argv) > 1 else Path(__file__).resolve().parents[3] / "SenarioOS" / "docs" / "pinmap.md"
out.write_text("\n".join(rows) + "\n")
print("pinmap written,", out)
